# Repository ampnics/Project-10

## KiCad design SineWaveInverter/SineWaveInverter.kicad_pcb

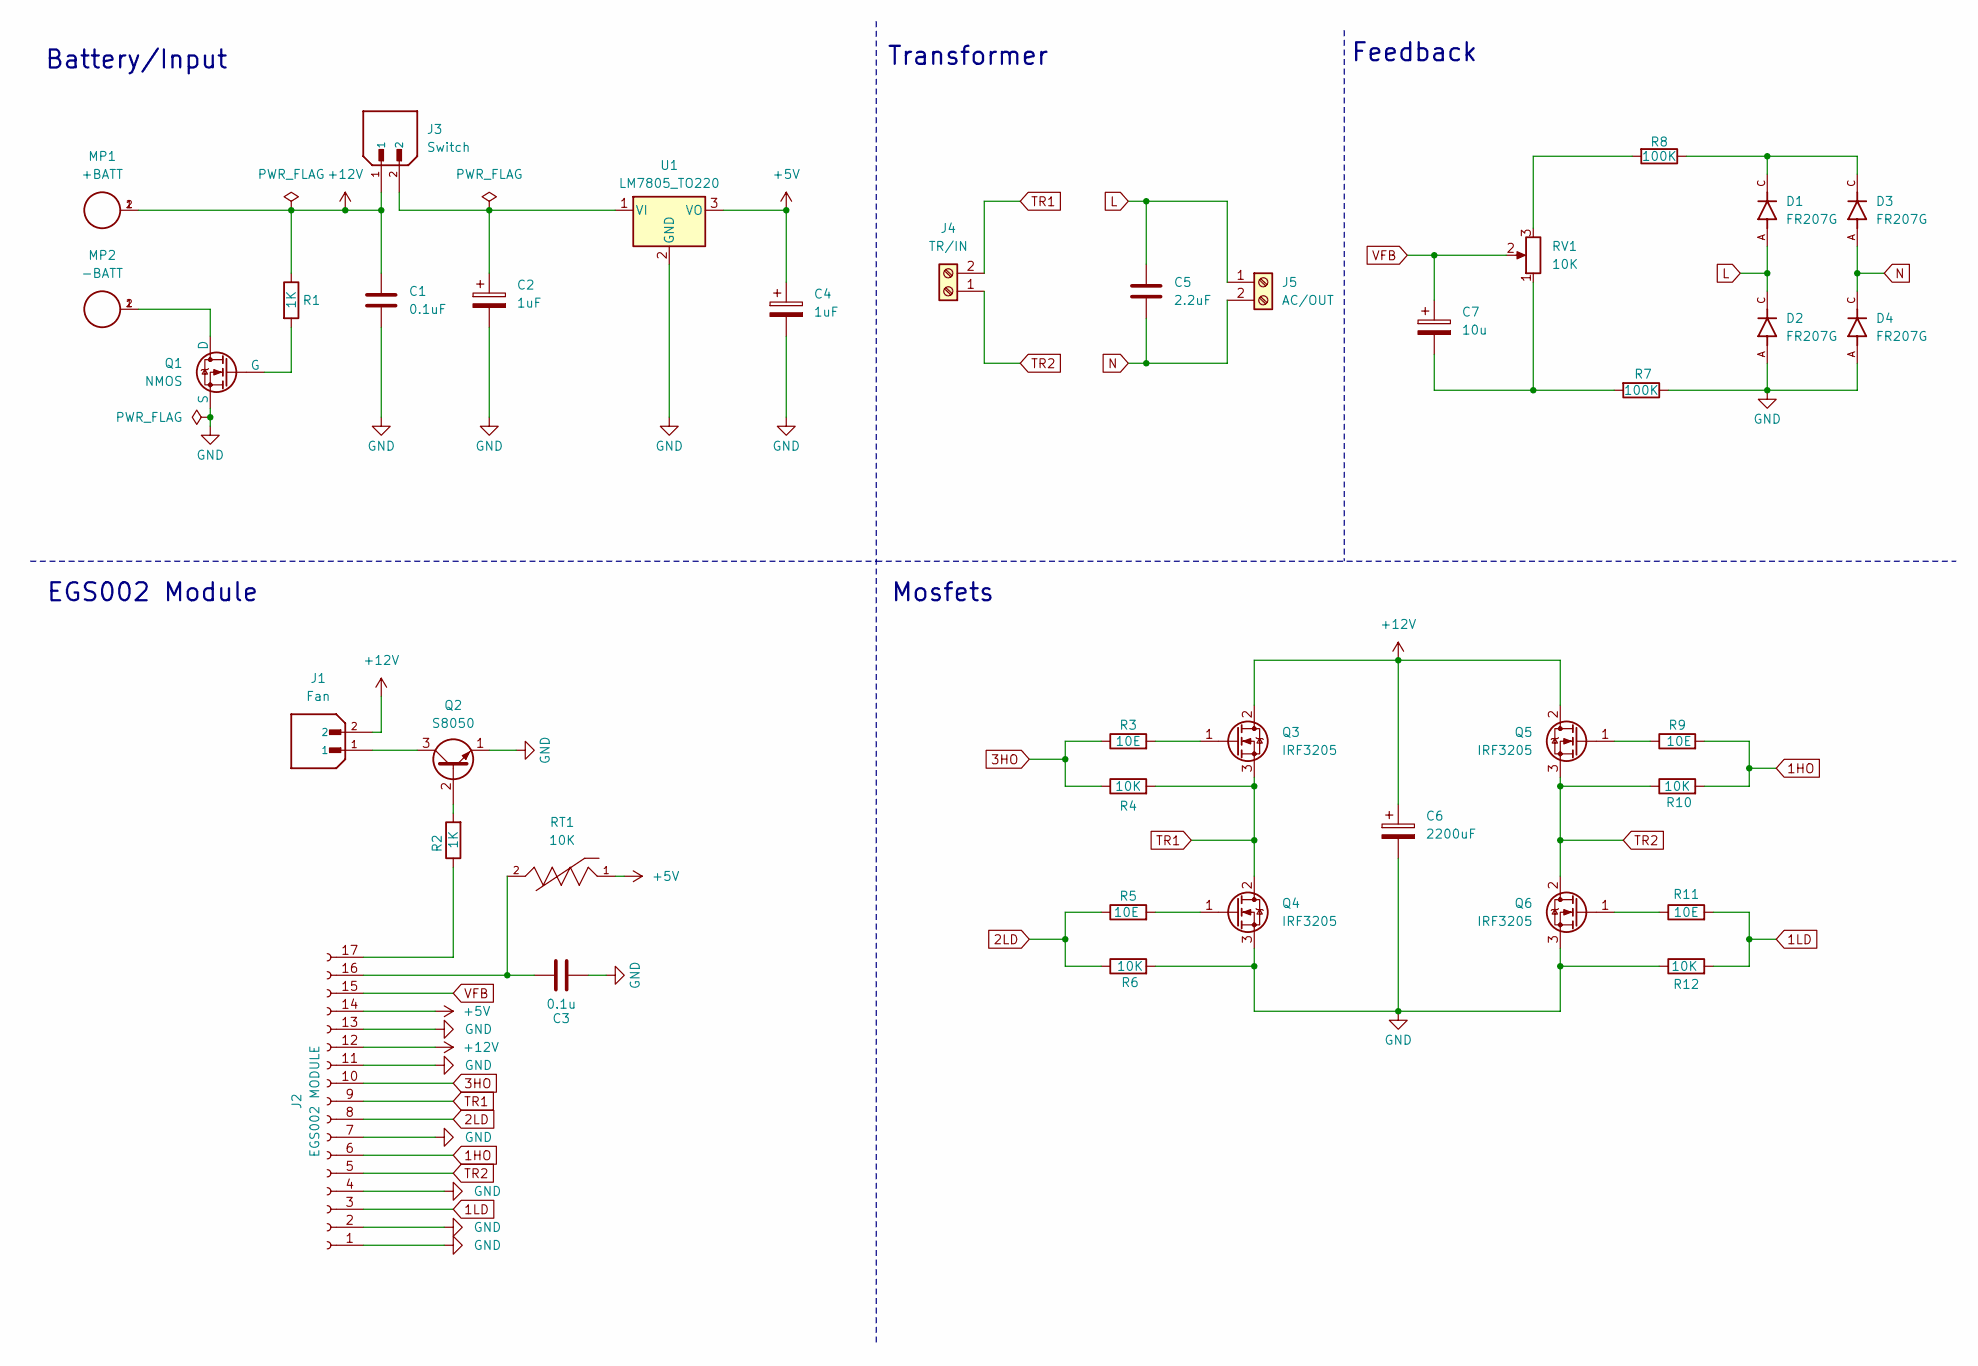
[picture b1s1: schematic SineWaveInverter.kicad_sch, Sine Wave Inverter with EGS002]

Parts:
C1: 0.1uF; C_Disc_D4.3mm_W1.9mm_P5.00mm
C2, C4: 1uF; CP_Radial_D5.0mm_P2.50mm
C3: 0.1u; C_Disc_D4.3mm_W1.9mm_P5.00mm
C5: 2.2uF; C_Rect_L16.5mm_W6.0mm_P15.00mm_MKT
C6: 2200uF; CP_Radial_D12.5mm_P5.00mm
C7: 10u; CP_Radial_D5.0mm_P2.50mm
D1, D2, D3, D4: FR207G; DIOAD1300W80L670D310; PARTREV F2105
J1: Fan; JST_B2B-XH-A__LF__SN_; PARTREV N/A
J2: EGS002 MODULE; PinSocket_1x17_P2.54mm_Vertical
J3: Switch; JST_B2B-XH-A__LF__SN_; PARTREV N/A
J4: TR/IN; TerminalBlock_bornier-2_P5.08mm
J5: AC/OUT; TerminalBlock_bornier-2_P5.08mm
MP1: +BATT; WA-MTAB_7471287; PART-NUMBER 7471287
MP2: -BATT; WA-MTAB_7471287; PART-NUMBER 7471287
Q1: NMOS; TO-252-2
Q2: S8050; TO-92_Inline
Q3, Q4, Q5, Q6: IRF3205; TO-220-3_Vertical
R1, R2: 1K; R_Axial_DIN0207_L6.3mm_D2.5mm_P7.62mm_Horizontal
R3, R5, R9, R11: 10E; R_Axial_DIN0207_L6.3mm_D2.5mm_P7.62mm_Horizontal
R4, R6, R10, R12: 10K; R_Axial_DIN0207_L6.3mm_D2.5mm_P7.62mm_Horizontal
R7, R8: 100K; R_Axial_DIN0207_L6.3mm_D2.5mm_P7.62mm_Horizontal
RT1: 10K; THERM_NXRT15WB333JA3A016; PARTREV N/A
RV1: 10K; Potentiometer_Bourns_3296W_Vertical
U1: LM7805_TO220; TO-220-3_Vertical

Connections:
1HO: J2.6, R9.2, R10.2
1LD: J2.3, R11.2, R12.2
2LD: J2.8, R5.1, R6.1
3HO: J2.10, R3.1, R4.1
+5V: C4.1, J2.14, RT1.1, U1.3 (VO)
+12V: C1.1, C6.1, J1.2, J2.12, J3.1, MP1.1, MP1.2, Q3.2 (D), Q5.2 (D), R1.1; also elsewhere on the board
GND: C1.2, C2.2, C3.2, C4.2, C6.2, D2.A, D4.A, J2.1, J2.2, J2.4, J2.7, J2.11, J2.13, Q1.3 (S), Q2.1 (E), Q4.3 (S), Q6.3 (S), R6.2, R7.1, R12.1, U1.2 (GND)
L: C5.1, D1.A, D2.C, J5.1
N: C5.2, D3.A, D4.C, J5.2
unnamed: C7.2, R7.2, RV1.1
unnamed: D1.C, D3.C, R8.1
unnamed: C3.1, J2.16, RT1.2
unnamed: J2.17, R2.1
unnamed: MP2.1, MP2.2, Q1.1 (D)
unnamed: Q1.2 (G), R1.2
unnamed: Q2.2 (B), R2.2
unnamed 16: J1.1, Q2.3 (C); also elsewhere on the board
unnamed: Q3.1 (G), R3.2
unnamed: Q4.1 (G), R5.2
unnamed: Q5.1 (G), R9.1
unnamed: Q6.1 (G), R11.1
unnamed: R8.2, RV1.3
unnamed 22: C2.1, J3.2, U1.1 (VI); also elsewhere on the board
TR1: J2.9, J4.2, Q3.3 (S), Q4.2 (D), R4.2
TR2: J2.5, J4.1, Q5.3 (S), Q6.2 (D), R10.1
VFB: C7.1, J2.15, RV1.2

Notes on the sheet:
Battery/Input
EGS002 Module
Transformer
Feedback
Mosfets

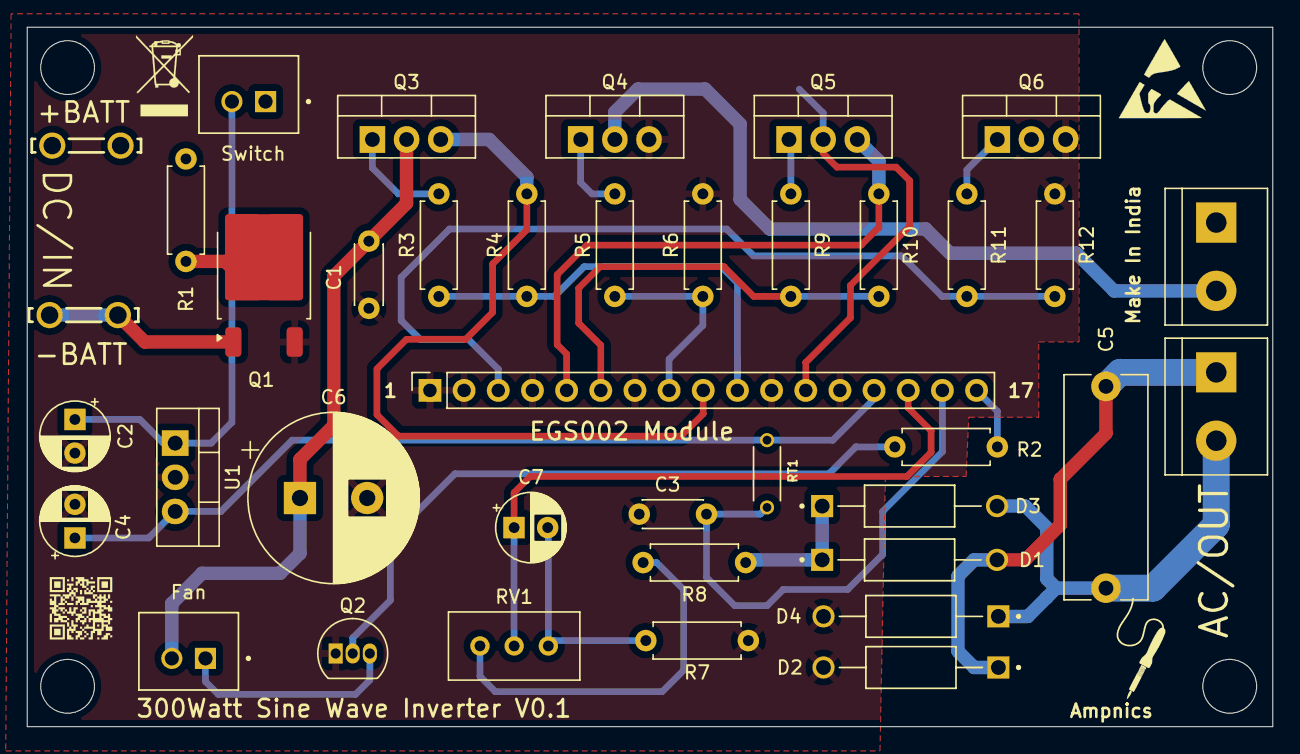
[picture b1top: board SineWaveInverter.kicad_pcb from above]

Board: 2 copper layers, 92.6 x 52.0 mm, 39 parts (0 on the bottom side), 26 nets.

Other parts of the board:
Fan: Fan; JST_B2B-XH-A__LF__SN_
Switch: Switch; JST_B2B-XH-A__LF__SN_

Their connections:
+12V: Fan.2, Switch.1; also elsewhere on the board
unnamed 16: Fan.1; also elsewhere on the board
unnamed 22: Switch.2; also elsewhere on the board

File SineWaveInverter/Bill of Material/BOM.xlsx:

Reference | Value | Footprint | Qty
C1 | 0.1uF | Capacitor_THT:C_Disc_D4.3mm_W1.9mm_P5.00mm | 1
C2,C4 | 1uF | Capacitor_THT:CP_Radial_D5.0mm_P2.50mm | 2
C3 | 0.1u | Capacitor_THT:C_Disc_D4.3mm_W1.9mm_P5.00mm | 1
C5 | 2.2uF | Capacitor_THT:C_Rect_L16.5mm_W6.0mm_P15.00mm_MKT | 1
C6 | 2200uF | Capacitor_THT:CP_Radial_D12.5mm_P5.00mm | 1
C7 | 10u | Capacitor_THT:CP_Radial_D5.0mm_P2.50mm | 1
D1,D2,D3,D4 | FR207G | FR207G:DIOAD1300W80L670D310 | 4
J1 | Fan | B2B-XH-A__LF__SN_:JST_B2B-XH-A__LF__SN_ | 1
J2 | EGS002 MODULE | Connector_PinSocket_2.54mm:PinSocket_1x17_P2.54mm_Vertical | 1
J3 | Switch | B2B-XH-A__LF__SN_:JST_B2B-XH-A__LF__SN_ | 1
J4 | TR/IN | TerminalBlock:TerminalBlock_bornier-2_P5.08mm | 1
J5 | AC/OUT | TerminalBlock:TerminalBlock_bornier-2_P5.08mm | 1
MP1 | #NAME? | WA-MTAB:WA-MTAB_7471287 | 1
MP2 | #NAME? | WA-MTAB:WA-MTAB_7471287 | 1
Q1 | NMOS | Package_TO_SOT_SMD:TO-252-2 | 1
Q2 | S8050 | Package_TO_SOT_THT:TO-92_Inline | 1
Q3,Q4,Q5,Q6 | IRF3205 | Package_TO_SOT_THT:TO-220-3_Vertical | 4
R1,R2 | 1K | Resistor_THT:R_Axial_DIN0207_L6.3mm_D2.5mm_P7.62mm_Horizontal | 2
R3,R5,R9,R11 | 10E | Resistor_THT:R_Axial_DIN0207_L6.3mm_D2.5mm_P7.62mm_Horizontal | 4
R4,R6,R10,R12,RT1,RV1 | 10K | -- mixed values -- | 6
R7,R8 | 100K | Resistor_THT:R_Axial_DIN0207_L6.3mm_D2.5mm_P7.62mm_Horizontal | 2
U1 | LM7805_TO220 | Package_TO_SOT_THT:TO-220-3_Vertical | 1
